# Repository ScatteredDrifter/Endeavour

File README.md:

# Endeavour | 10 Ortho Keyboard

An orthogonal  10u keyboard heavily inspired by [kb_elmo`s QEZ](https://github.com/kb-elmo/QEZ)

Used License for this project :: [Cern Open Hardware](/LICENSE)
by Evelyn~ Scattered Drifter 

---

### Current Status: 

- rev3 tested, minor issues fixed in 
- firmware for QMK was updated to newest version, can be found [here](https://github.com/ScatteredDrifter/vial-qmk/tree/scatteredDriftersBoards/keyboards/scattereddrifter/endeavour)
- ZMK firmware pending
- rev3 case available - yet I dislike it in its current state.

---

## Endeavour V³ released //
The third iteration introduced a complete redesign of the pcb primarily to accommodate the **RP2040** and **BAV70 diodes**.

 I tried creating a circular positioning pattern for the components where their center is set with the mcu itself. Due to reposition of every component I rerouted the whole board again; also because Endeavour V¹ was one of my first designs and you can tell it was. A new silkscreen for both front and back of the pcb sets a different theme and clutters the whole board with ASCII-rubbish. This came into my mind because any actual drawing or pattern idea I had was blocked by my miserable ability to create art.

A new **case** accompanies this revision. Its not entirely done neither am I satisfied with its look and design. My abilities with CAD are limited and I lack the endurance ( will to use Windows or learn an alternative software) and time to make a better one or to create an actual good / decent design. 

Nevertheless my current process is shared in [this folder](/cases_rev3).
I've **tested the case** with a previous rev pcb and could verify that its mostly working. 
The new **case utilizes tadpole mount** of some sort hence I **ought to write a build guide**. 

For the previous versions of the **PCB** and **Case** look at the folders below:

2. [Rev2](/rev2/rev2.md)

### Features |- Rev3:
- support for two encoders ( top left)(bottom row middle)
- RP2040 
- 3 IO Pins exposed via breakout 
- pinout for led-strip (WS28 and similarly supported)
- QMK / VIAL support ( zmk should be possible too ) 
- different layout options
- new **case** with tadpole mount

#### Layout:

---

## Images 

### Images of V³ PCB:

### Images of V³ case:
Those are only renders, however I've printed a small test version already. 

---

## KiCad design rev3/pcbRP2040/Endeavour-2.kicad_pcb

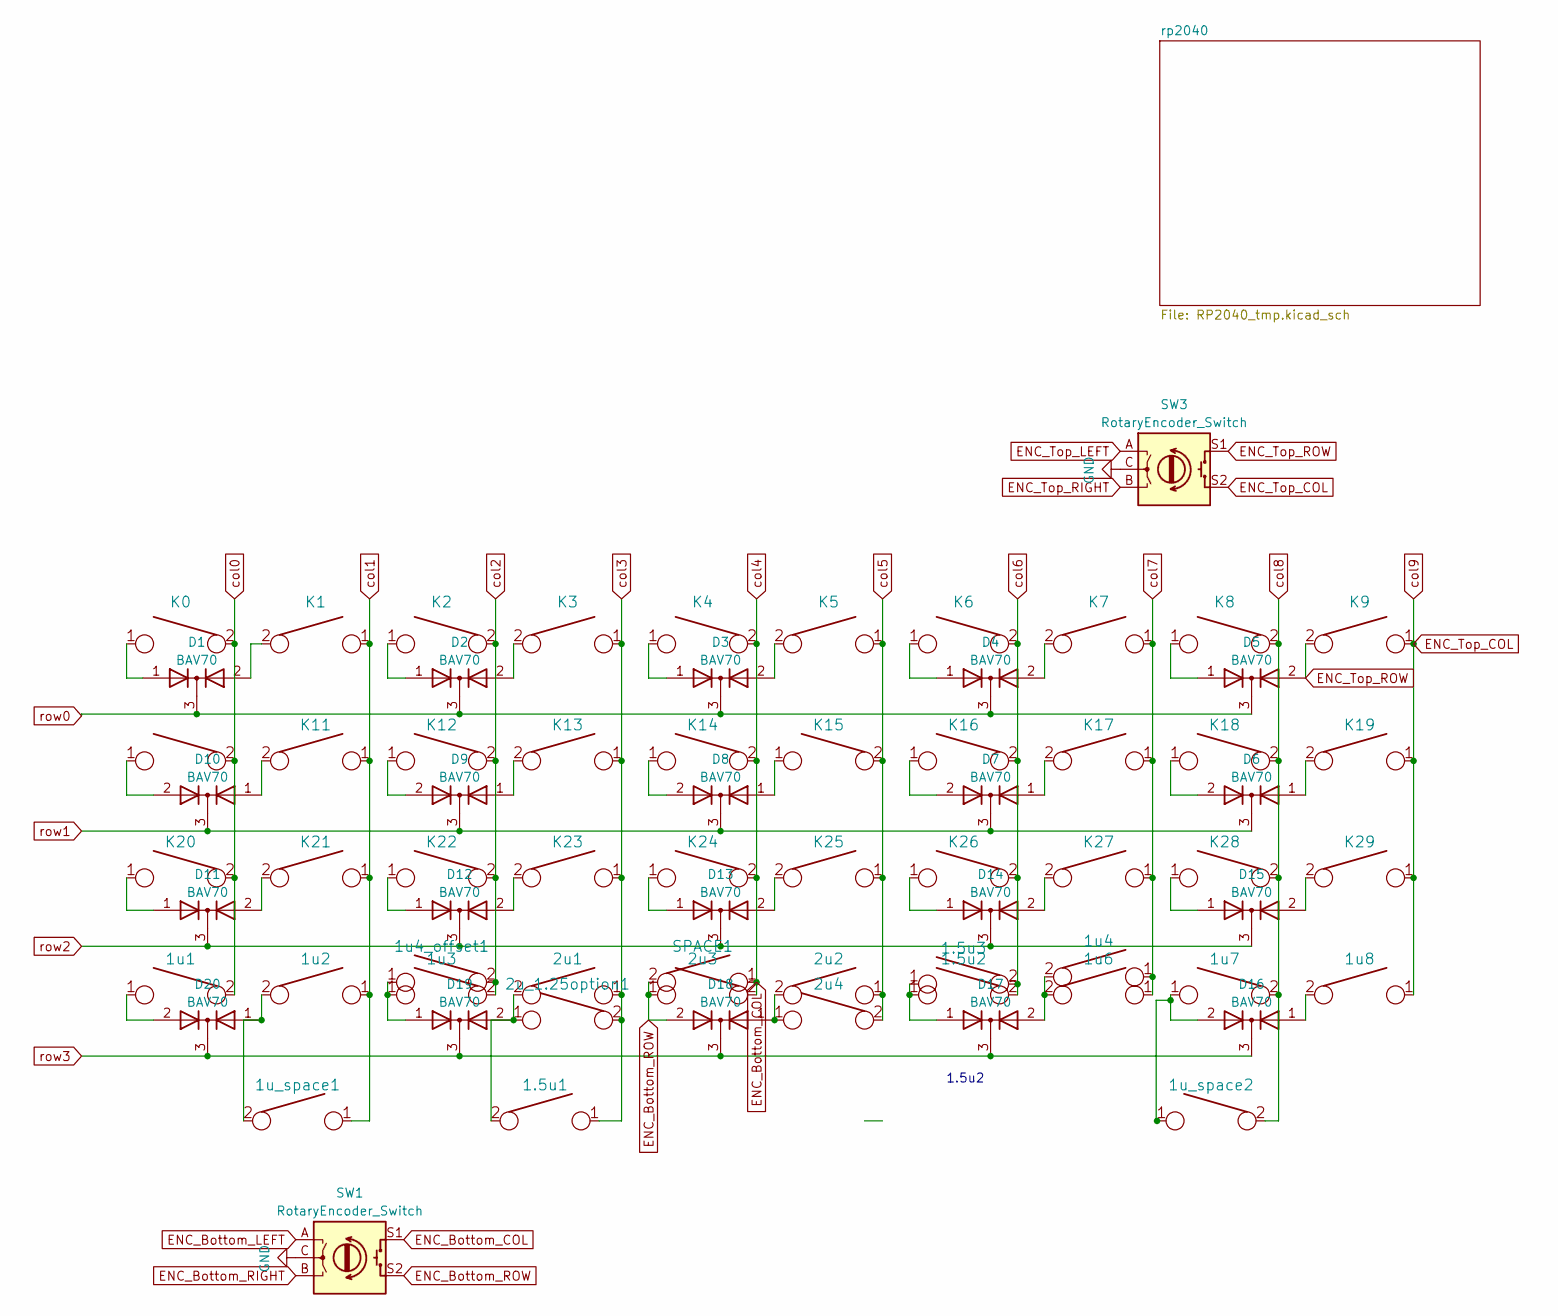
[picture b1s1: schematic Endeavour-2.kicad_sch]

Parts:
1.5u1, 1.5u2, 1.5u3: 1.5u; SW_MX_HS_1u_NOREF
1u1, 1u2, 1u3, 1u4, 1u4_offset1, 1u6, 1u7, 1u8, 1u_space1, 1u_space2: 1u; SW_MX_HS_1u_NOREF
2u1, 2u2, 2u3, 2u4, 2u_1.25option1: 2u; SW_MX_HS_1u_NOREF
D1, D2, D3, D4, D5, D6, D7, D8, D9, D10, D11, D12, D13, D14, D15, D16, D17, D18, D19, D20: BAV70; SOT-23
K0, K1, K2, K3, K4, K5, K6, K7, K8, K9, K10, K11, K12, K13, K14, K15, K16, K17, K18, K19, K20, K21, K22, K23, K24, K25, K26, K27, K28, K29: 1u; SW_MX_HS_1u_NOREF
SPACE1: 7u; SW_MX_HS_1u_NOREF
SW1, SW3: RotaryEncoder_Switch; ROT_Alps_EC11E-Switch

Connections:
ENC_Bottom_COL: 2u3.2, K4.2, K14.2, K24.2, SPACE1.1, SW1.S1; also elsewhere on the board
ENC_Bottom_LEFT: SW1.A; also elsewhere on the board
ENC_Bottom_RIGHT: SW1.B; also elsewhere on the board
ENC_Bottom_ROW: 2u3.1, D18.2 (A), SPACE1.2, SW1.S2
ENC_Top_COL: 1u8.1, K9.1, K19.1, K29.1, SW3.S2; also elsewhere on the board
ENC_Top_LEFT: SW3.A; also elsewhere on the board
ENC_Top_RIGHT: SW3.B; also elsewhere on the board
ENC_Top_ROW: D5.2 (A), K9.2, SW3.S1
GND: SW1.C, SW3.C; also elsewhere on the board
unnamed: 1.5u1.2, 2u1.2, 2u_1.25option1.1, D19.2 (A)
unnamed: 1.5u2.1, 1.5u3.1, D17.1 (A)
unnamed: 1u1.1, D20.2 (A)
unnamed: 1u2.2, 1u_space1.2, D20.1 (A)
unnamed: 1u3.1, 1u4_offset1.1, D19.1 (A)
unnamed: 1u4.2, 1u6.2, D17.2 (A)
unnamed: 1u7.1, 1u_space2.1, D16.2 (A)
unnamed: 1u8.2, D16.1 (A)
unnamed: 2u2.2, 2u4.1, D18.1 (A)
unnamed: D1.1 (A), K0.1
unnamed: D1.2 (A), K1.2
unnamed: D2.1 (A), K2.1
unnamed: D2.2 (A), K3.2
unnamed: D3.1 (A), K4.1
unnamed: D3.2 (A), K5.2
unnamed: D4.1 (A), K6.1
unnamed: D4.2 (A), K7.2
unnamed: D5.1 (A), K8.1
unnamed: D6.1 (A), K19.2
unnamed: D6.2 (A), K18.1
unnamed: D7.1 (A), K17.2
unnamed: D7.2 (A), K16.1
unnamed: D8.1 (A), K15.1
unnamed: D8.2 (A), K14.1
unnamed: D9.1 (A), K13.2
unnamed: D9.2 (A), K12.1
unnamed: D10.1 (A), K11.2
unnamed: D10.2 (A), K10.1
unnamed: D11.1 (A), K20.1
unnamed: D11.2 (A), K21.2
unnamed: D12.1 (A), K22.1
unnamed: D12.2 (A), K23.2
unnamed: D13.1 (A), K24.1
unnamed: D13.2 (A), K25.2
unnamed: D14.1 (A), K26.1
unnamed: D14.2 (A), K27.2
unnamed: D15.1 (A), K28.1
unnamed: D15.2 (A), K29.2
col0: 1u1.2, K0.2, K10.2, K20.2; also elsewhere on the board
col1: 1u2.1, 1u_space1.1, K1.1, K11.1, K21.1; also elsewhere on the board
col2: 1u3.2, 1u4_offset1.2, K2.2, K12.2, K22.2; also elsewhere on the board
col3: 1.5u1.1, 2u1.1, 2u_1.25option1.2, K3.1, K13.1, K23.1; also elsewhere on the board
col5: 2u2.1, 2u4.2, K5.1, K15.2, K25.1; also elsewhere on the board
col6: 1.5u2.2, 1.5u3.2, K6.2, K16.2, K26.2; also elsewhere on the board
col7: 1u4.1, 1u6.1, K7.1, K17.1, K27.1; also elsewhere on the board
col8: 1u7.2, 1u_space2.2, K8.2, K18.2, K28.2; also elsewhere on the board
row0: D1.3 (K), D2.3 (K), D3.3 (K), D4.3 (K), D5.3 (K); also elsewhere on the board
row1: D6.3 (K), D7.3 (K), D8.3 (K), D9.3 (K), D10.3 (K); also elsewhere on the board
row2: D11.3 (K), D12.3 (K), D13.3 (K), D14.3 (K), D15.3 (K); also elsewhere on the board
row3: D16.3 (K), D17.3 (K), D18.3 (K), D19.3 (K), D20.3 (K); also elsewhere on the board

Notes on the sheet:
1.5u2

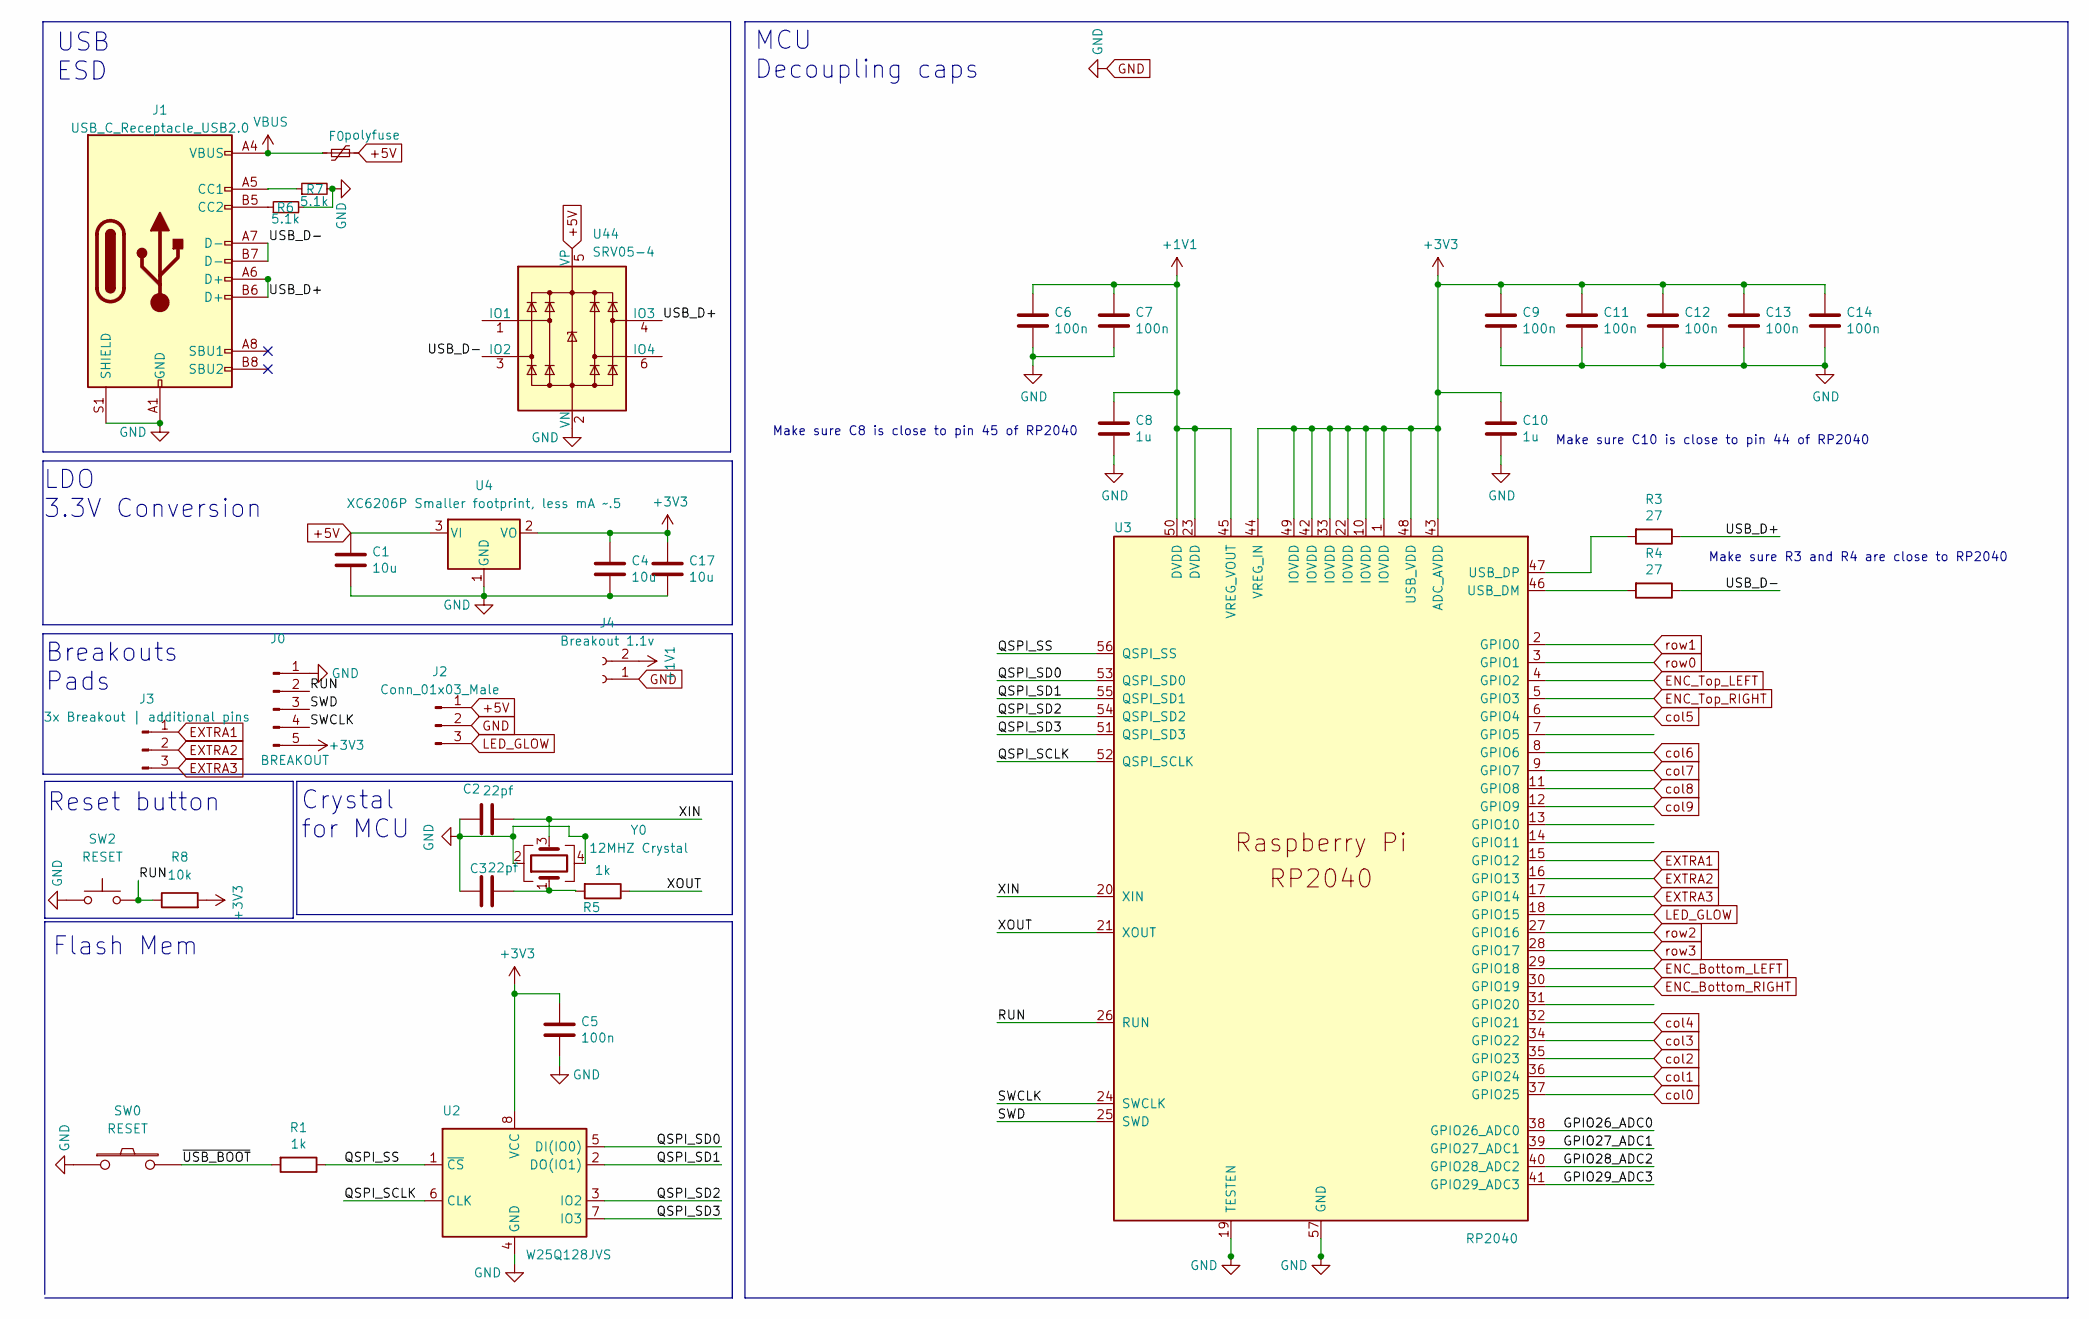
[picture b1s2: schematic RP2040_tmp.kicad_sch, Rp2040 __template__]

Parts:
C1, C4, C17: 10u; C_0805_2012Metric; LCSC C91245
C2, C3: 22pf; C_0805_2012Metric; LCSC C1804
C5, C6, C7, C9, C11, C12, C13, C14: 100n; C_0805_2012Metric; LCSC C49678
C8, C10: 1u; C_0805_2012Metric; LCSC C28323
F0: polyfuse; Fuse_1206_3216Metric; LCSC C69688
J0: BREAKOUT; PinSocket_1x05_P2.54mm_Vertical
J1: USB_C_Receptacle_USB2.0; USB_C_Receptacle_HRO_TYPE-C-31-M-12; LCSC C165948
J2: Conn_01x03_Male; PinSocket_1x03_P2.00mm_Vertical
J3: 3x Breakout | additional pins; PinHeader_1x03_P2.54mm_Vertical
J4: Breakout 1.1v; PinHeader_1x02_P2.54mm_Vertical
R1, R5: 1k; R_0805_2012Metric; LCSC C115316
R3, R4: 27; R_0805_2012Metric; LCSC C104170
R6, R7: 5.1k; R_0805_2012Metric; LCSC C27834
R8: 10k; R_0805_2012Metric; LCSC C115309
SW0, SW2: RESET; SW_SPST_TL3342; LCSC C2886894
U2: W25Q128JVS; SOIC-8_5.23x5.23mm_P1.27mm; LCSC C97521
U3: RP2040; RP2040-QFN-56; LCSC C2040
U4: XC6206P Smaller footprint, less mA ~.5; SOT-23; LCSC C347376
U44: SRV05-4; SOT-23-6; LCSC C85364
Y0: 12MHZ Crystal; Crystal_SMD_3225-4Pin_3.2x2.5mm; LCSC C9002

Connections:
+1V1: C6.1, C7.1, C8.1, J4.2, U3.23 (DVDD), U3.45 (VREG_VOUT), U3.50 (DVDD)
+3V3: C4.1, C5.1, C9.1, C10.1, C11.1, C12.1, C13.1, C14.1, C17.1, J0.5, R8.2, U2.8 (VCC), U3.1 (IOVDD), U3.10 (IOVDD), U3.22 (IOVDD), U3.33 (IOVDD), U3.42 (IOVDD), U3.43 (ADC_AVDD), U3.44 (VREG_IN), U3.48 (USB_VDD), U3.49 (IOVDD), U4.2 (VO)
+5V: C1.1, F0.2, J2.1, U4.3 (VI), U44.5 (VP)
/rp2040/GPIO26_ADC0: U3.38 (GPIO26_ADC0)
/rp2040/GPIO27_ADC1: U3.39 (GPIO27_ADC1)
/rp2040/GPIO28_ADC2: U3.40 (GPIO28_ADC2)
/rp2040/GPIO29_ADC3: U3.41 (GPIO29_ADC3)
/rp2040/QSPI_SCLK: U2.6 (CLK), U3.52 (QSPI_SCLK)
/rp2040/QSPI_SD0: U2.5 (DI(IO0)), U3.53 (QSPI_SD0)
/rp2040/QSPI_SD1: U2.2 (DO(IO1)), U3.55 (QSPI_SD1)
/rp2040/QSPI_SD2: U2.3 (IO2), U3.54 (QSPI_SD2)
/rp2040/QSPI_SD3: U2.7 (IO3), U3.51 (QSPI_SD3)
/rp2040/QSPI_SS: R1.1, U2.1 (~CS), U3.56 (QSPI_SS)
/rp2040/RUN: J0.2, R8.1, SW2.2, U3.26 (RUN)
/rp2040/SWCLK: J0.4, U3.24 (SWCLK)
/rp2040/SWD: J0.3, U3.25 (SWD)
/rp2040/USB_D+: J1.A6 (D+), J1.B6 (D+), R3.1, U44.4 (IO3)
/rp2040/USB_D-: J1.A7 (D-), J1.B7 (D-), R4.1, U44.3 (IO2)
/rp2040/XIN: C2.1, U3.20 (XIN), Y0.3
/rp2040/XOUT: R5.1, U3.21 (XOUT)
/rp2040/~USB_BOOT: R1.2, SW0.2
ENC_Bottom_COL: U3.32 (GPIO21); also elsewhere on the board
ENC_Bottom_LEFT: U3.29 (GPIO18); also elsewhere on the board
ENC_Bottom_RIGHT: U3.30 (GPIO19); also elsewhere on the board
ENC_Top_COL: U3.12 (GPIO9); also elsewhere on the board
ENC_Top_LEFT: U3.4 (GPIO2); also elsewhere on the board
ENC_Top_RIGHT: U3.5 (GPIO3); also elsewhere on the board
EXTRA1: J3.1, U3.15 (GPIO12)
EXTRA2: J3.2, U3.16 (GPIO13)
EXTRA3: J3.3, U3.17 (GPIO14)
GND: C1.2, C2.2, C3.2, C4.2, C5.2, C6.2, C7.2, C8.2, C9.2, C10.2, C11.2, C12.2, C13.2, C14.2, C17.2, J0.1, J1.A1 (GND), J1.A12 (GND), J1.B1 (GND), J1.B12 (GND), J1.S1 (SHIELD), J2.2, J4.1, R6.2, R7.2, SW0.1, SW2.1, U2.4 (GND), U3.19 (TESTEN), U3.57 (GND), U4.1 (GND), U44.2 (VN), Y0.2, Y0.4; also elsewhere on the board
LED_GLOW: J2.3, U3.18 (GPIO15)
unnamed: C3.1, R5.2, Y0.1
unnamed: J1.A5 (CC1), R7.1
unnamed: J1.B5 (CC2), R6.1
unnamed: R4.2, U3.46 (USB_DM)
unnamed: R3.2, U3.47 (USB_DP)
VBUS: F0.1, J1.A4 (VBUS), J1.A9 (VBUS), J1.B4 (VBUS), J1.B9 (VBUS)
col0: U3.37 (GPIO25); also elsewhere on the board
col1: U3.36 (GPIO24); also elsewhere on the board
col2: U3.35 (GPIO23); also elsewhere on the board
col3: U3.34 (GPIO22); also elsewhere on the board
col5: U3.6 (GPIO4); also elsewhere on the board
col6: U3.8 (GPIO6); also elsewhere on the board
col7: U3.9 (GPIO7); also elsewhere on the board
col8: U3.11 (GPIO8); also elsewhere on the board
row0: U3.3 (GPIO1); also elsewhere on the board
row1: U3.2 (GPIO0); also elsewhere on the board
row2: U3.27 (GPIO16); also elsewhere on the board
row3: U3.28 (GPIO17); also elsewhere on the board

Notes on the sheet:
USB ESD
Make sure C8 is close to pin 45 of RP2040
Breakouts Pads
Make sure R3 and R4 are close to RP2040
Crystal for MCU
Flash Mem
MCU Decoupling caps
Make sure C10 is close to pin 44 of RP2040
Reset button
LDO 3.3V Conversion

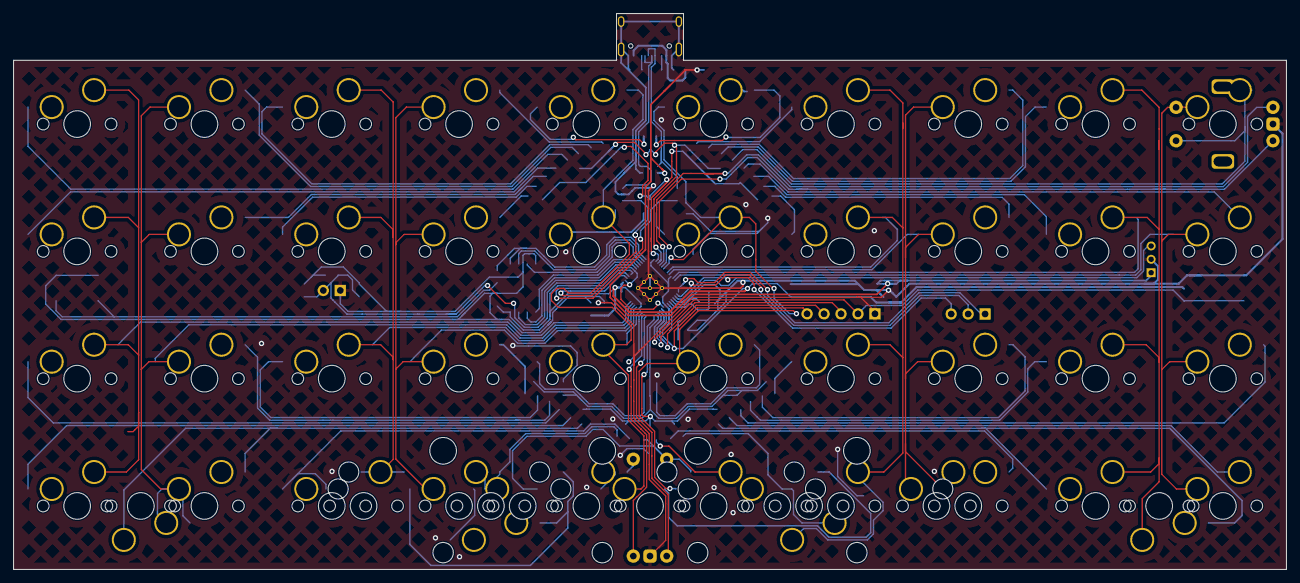
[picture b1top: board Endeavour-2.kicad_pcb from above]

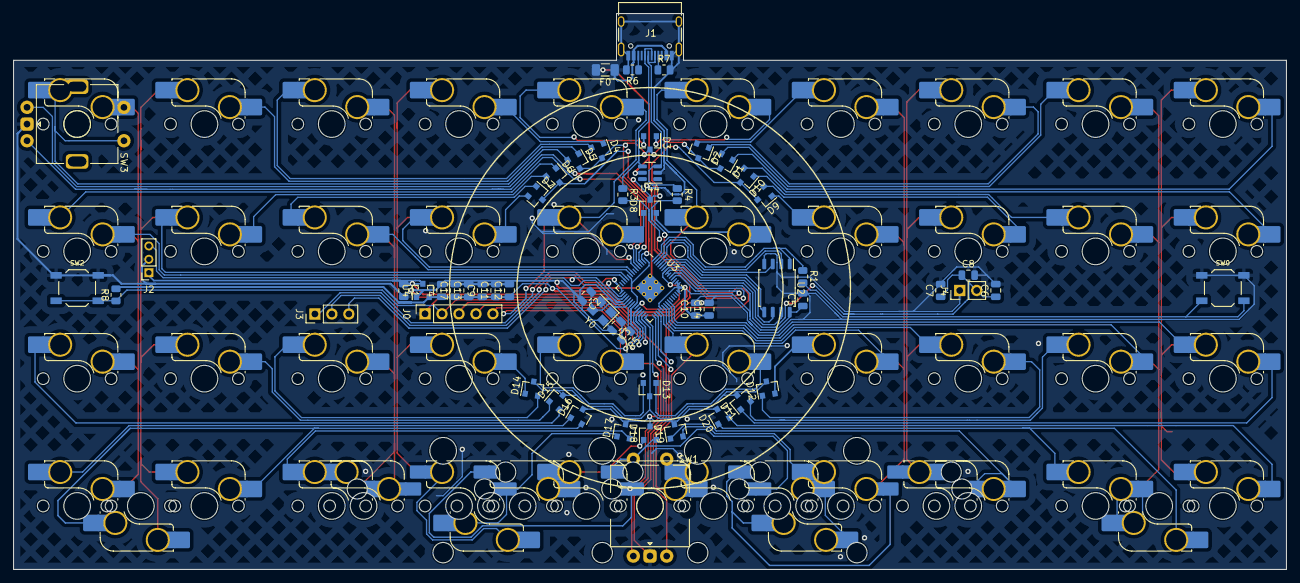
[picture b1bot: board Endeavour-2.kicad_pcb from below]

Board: 2 copper layers, 190.5 x 83.2 mm, 106 parts (106 on the bottom side), 86 nets.

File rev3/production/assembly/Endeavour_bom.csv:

Comment,Designator,Footprint,LCSC
"1.5u","1.5u1,1.5u2,1.5u3","marbastlib-mx:SW_MX_HS_1u_NOREF",""
"1u","K0,K1,K2,K3,K4,K5,K6,K7,K8,K9,K10,1u1,1u_space1,K11,1u2,1u_space2,K12,1u3,K13,1u4,K14,K15,1u6,K16,1u7,K17,1u8,K18,K19,K20,K21,K22,K23,K24,K25,K26,K27,K28,K29,1u4_offset1","marbastlib-mx:SW_MX_HS_1u_NOREF",""
"2u","2u1,2u2,2u3,2u4,2u_1.25option1","marbastlib-mx:SW_MX_HS_1u_NOREF",""
"10u","C1,C4,C17","Capacitor_SMD:C_0805_2012Metric","C91245"
"22pf","C2,C3","Capacitor_SMD:C_0805_2012Metric","C1804"
"100n","C5,C6,C7,C9,C11,C12,C13,C14","Capacitor_SMD:C_0805_2012Metric","C49678"
"1u","C8,C10","Capacitor_SMD:C_0805_2012Metric","C28323"
"BAV70","D1,D2,D3,D4,D5,D6,D7,D8,D9,D10,D11,D12,D13,D14,D15,D16,D17,D18,D19,D20","Package_TO_SOT_SMD:SOT-23","C181110"
"polyfuse","F0","Fuse:Fuse_1206_3216Metric","C69688"
"BREAKOUT","J0","Connector_PinSocket_2.54mm:PinSocket_1x05_P2.54mm_Vertical",""
"USB_C_Receptacle_USB2.0","J1","Connector_USB:USB_C_Receptacle_HRO_TYPE-C-31-M-12","C165948"
"Conn_01x03_Male","J2","Connector_PinSocket_2.00mm:PinSocket_1x03_P2.00mm_Vertical",""
"3x Breakout | additional pins","J3","Connector_PinHeader_2.54mm:PinHeader_1x03_P2.54mm_Vertical",""
"Breakout 1.1v","J4","Connector_PinHeader_2.54mm:PinHeader_1x02_P2.54mm_Vertical",""
"1k","R1,R5","Resistor_SMD:R_0805_2012Metric","C115316"
"27","R3,R4","Resistor_SMD:R_0805_2012Metric","C104170"
"5.1k","R6,R7","Resistor_SMD:R_0805_2012Metric","C27834"
"10k","R8","Resistor_SMD:R_0805_2012Metric","C115309"
"7u","SPACE1","marbastlib-mx:SW_MX_HS_1u_NOREF",""
"RESET ","SW0","Keebio-Parts:SW_SPST_TL3342","C2886894"
"RotaryEncoder_Switch","SW1,SW3","marbastlib-various:ROT_Alps_EC11E-Switch",""
"RESET","SW2","Keebio-Parts:SW_SPST_TL3342","C2886894"
"W25Q128JVS","U2","Package_SO:SOIC-8_5.23x5.23mm_P1.27mm","C97521"
"RP2040","U3","RP2040:RP2040-QFN-56","C2040"
"XC6206P Smaller footprint, less mA ~.5","U4","Package_TO_SOT_SMD:SOT-23","C347376"
"SRV05-4","U44","Package_TO_SOT_SMD:SOT-23-6","C85364"
"12MHZ Crystal ","Y0","Crystal:Crystal_SMD_3225-4Pin_3.2x2.5mm","C9002"

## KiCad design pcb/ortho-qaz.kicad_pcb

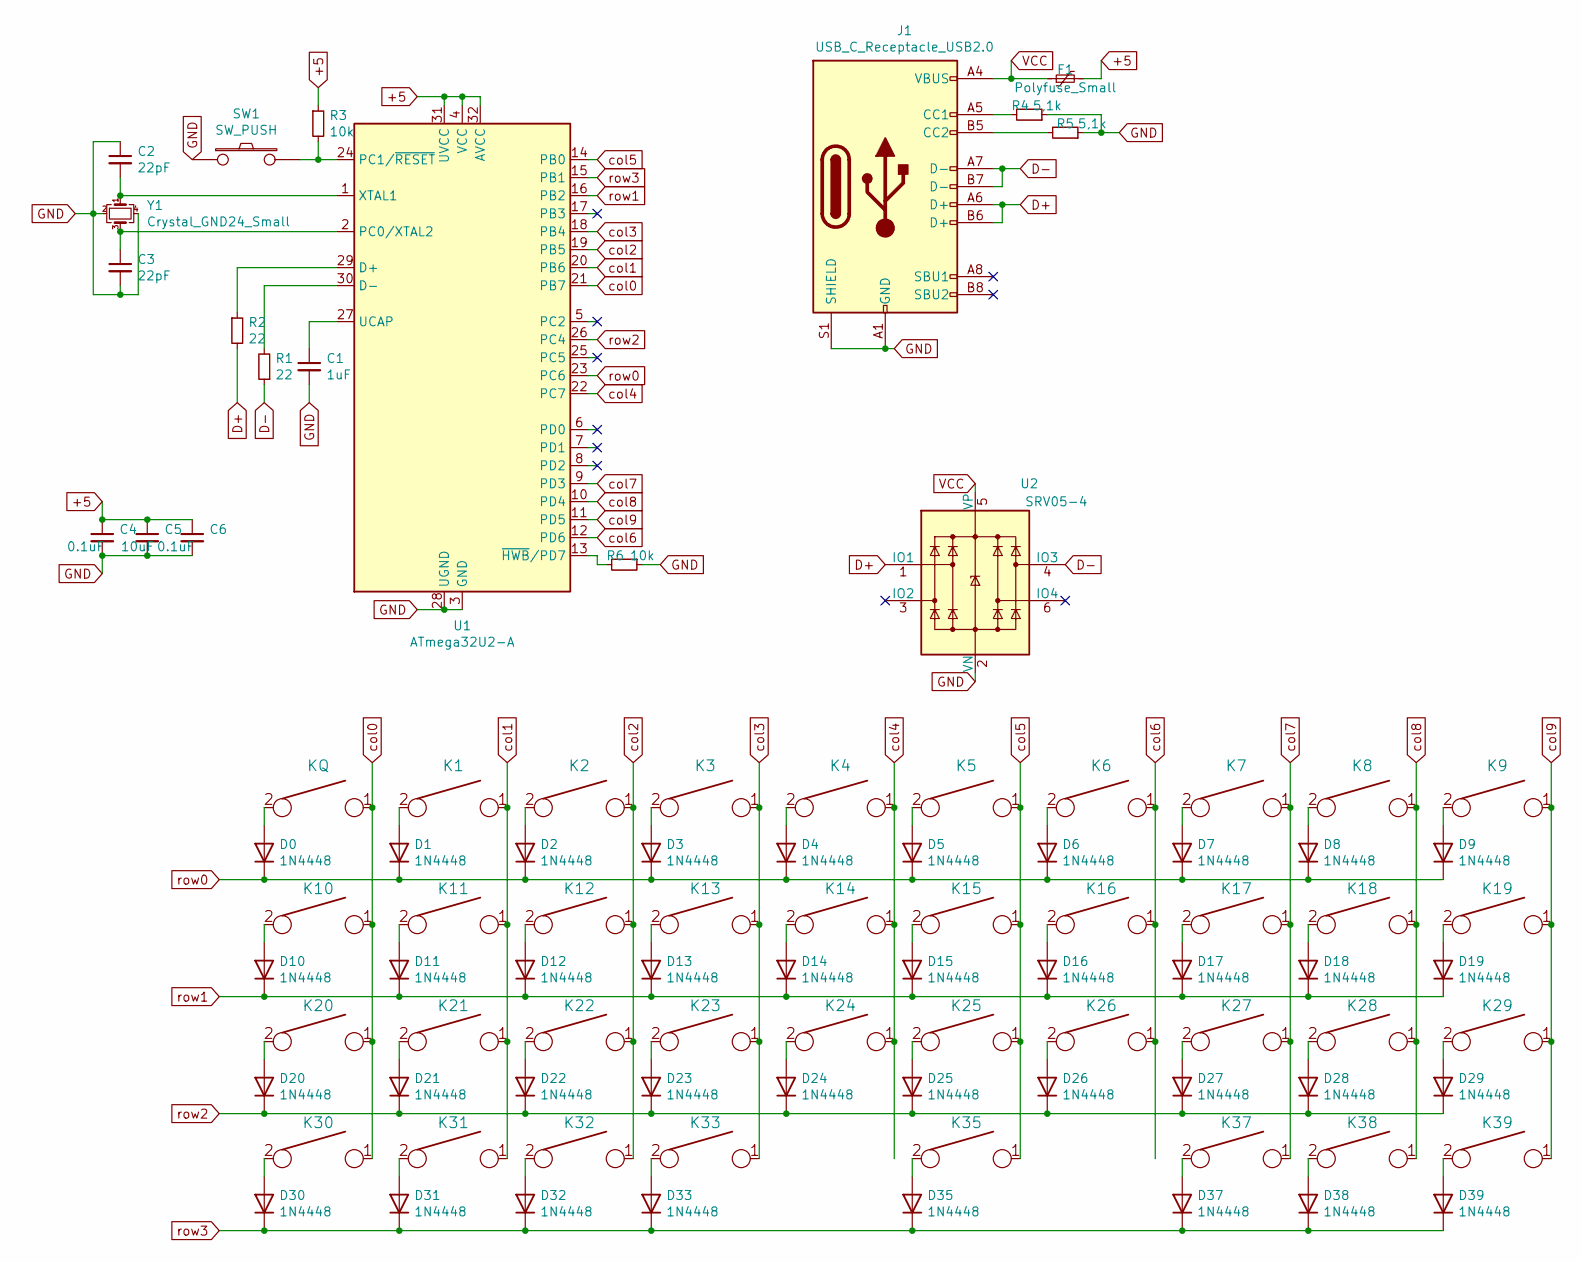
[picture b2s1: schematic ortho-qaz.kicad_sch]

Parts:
C1: 1uF; C_0805_2012Metric; LCSC C28323
C2, C3: 22pF; C_0805_2012Metric; LCSC C1804
C4, C6: 0.1uF; C_0805_2012Metric; LCSC C49678
C5: 10uF; C_0805_2012Metric; LCSC C91245
D0, D1, D2, D3, D4, D5, D6, D7, D8, D9, D10, D11, D12, D13, D14, D15, D16, D17, D18, D19, D20, D21, D22, D23, D24, D25, D26, D27, D28, D29, D30, D31, D32, D33, D35, D37, D38, D39: 1N4448; D_SOD123; LCSC C2128
F1: Polyfuse_Small; Fuse_1206_3216Metric; LCSC C69688
J1: USB_C_Receptacle_USB2.0; USB_C_Receptacle_HRO_TYPE-C-31-M-12; LCSC C165948
K1, K2, K3, K4, K5, K6, K7, K8, K9, K10, K11, K12, K13, K14, K15, K16, K17, K18, K19, K20, K21, K22, K23, K24, K25, K26, K27, K28, K29, K30, K31, K32, K33, K35, K37, K38, K39: KEYSW; Kailh_socket_MX_optional
KQ: KEYSW; Kailh_socket_MX_optional
R1, R2: 22; R_0805_2012Metric; LCSC C17561
R3, R6: 10k; R_0805_2012Metric; LCSC C17414
R4, R5: 5,1k; R_0805_2012Metric; LCSC C27834
SW1: SW_PUSH; SW_SPST_TL3342; LCSC C318884
U1: ATmega32U2-A; TQFP-32_7x7mm_P0.8mm; LCSC C618733
U2: SRV05-4; SOT-23-6; LCSC C85364
Y1: Crystal_GND24_Small; Crystal_SMD_3225-4Pin_3.2x2.5mm; LCSC C13738

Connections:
+5: C4.1, C5.1, C6.1, F1.2, R3.1, U1.4 (VCC), U1.31 (UVCC), U1.32 (AVCC)
D+: J1.A6 (D+), J1.B6 (D+), R2.2, U2.1 (IO1)
D-: J1.A7 (D-), J1.B7 (D-), R1.1, U2.4 (IO3)
GND: C1.2, C2.1, C3.2, C4.2, C5.2, C6.2, J1.A1 (GND), J1.A12 (GND), J1.B1 (GND), J1.B12 (GND), J1.S1 (SHIELD), R4.1, R5.1, R6.1, SW1.1, U1.3 (GND), U1.28 (UGND), U2.2 (VN), Y1.2, Y1.4
unnamed: C1.1, U1.27 (UCAP)
unnamed: C2.2, U1.1 (XTAL1), Y1.1
unnamed: C3.1, U1.2 (PC0/XTAL2), Y1.3
unnamed 7: D0.2 (A), KQ.2; also elsewhere on the board
unnamed: D1.2 (A), K1.2
unnamed: D2.2 (A), K2.2
unnamed: D3.2 (A), K3.2
unnamed: D4.2 (A), K4.2
unnamed: D5.2 (A), K5.2
unnamed: D6.2 (A), K6.2
unnamed: D7.2 (A), K7.2
unnamed: D8.2 (A), K8.2
unnamed: D9.2 (A), K9.2
unnamed: D10.2 (A), K10.2
unnamed: D11.2 (A), K11.2
unnamed: D12.2 (A), K12.2
unnamed: D13.2 (A), K13.2
unnamed: D14.2 (A), K14.2
unnamed: D15.2 (A), K15.2
unnamed: D16.2 (A), K16.2
unnamed: D17.2 (A), K17.2
unnamed: D18.2 (A), K18.2
unnamed: D19.2 (A), K19.2
unnamed: D20.2 (A), K20.2
unnamed: D21.2 (A), K21.2
unnamed: D22.2 (A), K22.2
unnamed: D23.2 (A), K23.2
unnamed: D24.2 (A), K24.2
unnamed: D25.2 (A), K25.2
unnamed: D26.2 (A), K26.2
unnamed: D27.2 (A), K27.2
unnamed: D28.2 (A), K28.2
unnamed: D29.2 (A), K29.2
unnamed: D30.2 (A), K30.2
unnamed: D31.2 (A), K31.2
unnamed: D32.2 (A), K32.2
unnamed: D33.2 (A), K33.2
unnamed: D35.2 (A), K35.2
unnamed: D37.2 (A), K37.2
unnamed: D38.2 (A), K38.2
unnamed: D39.2 (A), K39.2
unnamed: J1.A5 (CC1), R4.2
unnamed: J1.B5 (CC2), R5.2
unnamed: R1.2, U1.30 (D-)
unnamed: R2.1, U1.29 (D+)
unnamed: R3.2, SW1.2, U1.24 (PC1/~RESET)
unnamed: R6.2, U1.13 (~HWB/PD7)
VCC: F1.1, J1.A4 (VBUS), J1.A9 (VBUS), J1.B4 (VBUS), J1.B9 (VBUS), U2.5 (VP)
col0: K10.1, K20.1, K30.1, KQ.1, U1.21 (PB7); also elsewhere on the board
col1: K1.1, K11.1, K21.1, K31.1, U1.20 (PB6)
col2: K2.1, K12.1, K22.1, K32.1, U1.19 (PB5)
col3: K3.1, K13.1, K23.1, K33.1, U1.18 (PB4)
col4: K4.1, K14.1, K24.1, U1.22 (PC7)
col5: K5.1, K15.1, K25.1, K35.1, U1.14 (PB0)
col6: K6.1, K16.1, K26.1, U1.12 (PD6)
col7: K7.1, K17.1, K27.1, K37.1, U1.9 (PD3)
col8: K8.1, K18.1, K28.1, K38.1, U1.10 (PD4)
col9: K9.1, K19.1, K29.1, K39.1, U1.11 (PD5)
row0: D0.1 (K), D1.1 (K), D2.1 (K), D3.1 (K), D4.1 (K), D5.1 (K), D6.1 (K), D7.1 (K), D8.1 (K), D9.1 (K), U1.23 (PC6)
row1: D10.1 (K), D11.1 (K), D12.1 (K), D13.1 (K), D14.1 (K), D15.1 (K), D16.1 (K), D17.1 (K), D18.1 (K), D19.1 (K), U1.16 (PB2)
row2: D20.1 (K), D21.1 (K), D22.1 (K), D23.1 (K), D24.1 (K), D25.1 (K), D26.1 (K), D27.1 (K), D28.1 (K), D29.1 (K), U1.26 (PC4)
row3: D30.1 (K), D31.1 (K), D32.1 (K), D33.1 (K), D35.1 (K), D37.1 (K), D38.1 (K), D39.1 (K), U1.15 (PB1)

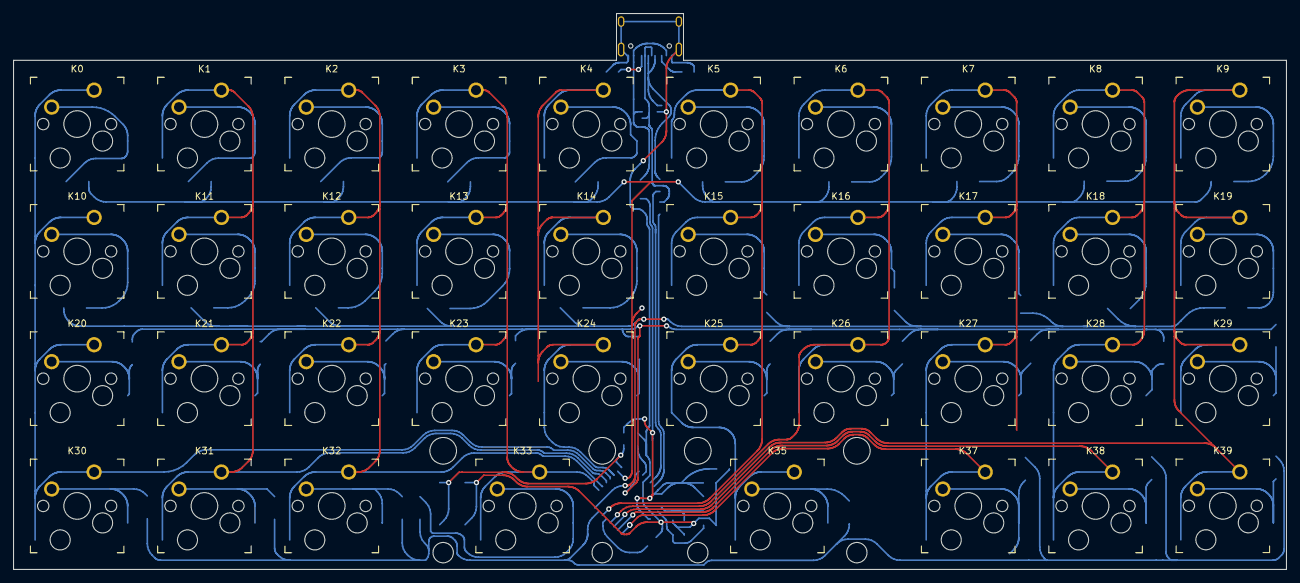
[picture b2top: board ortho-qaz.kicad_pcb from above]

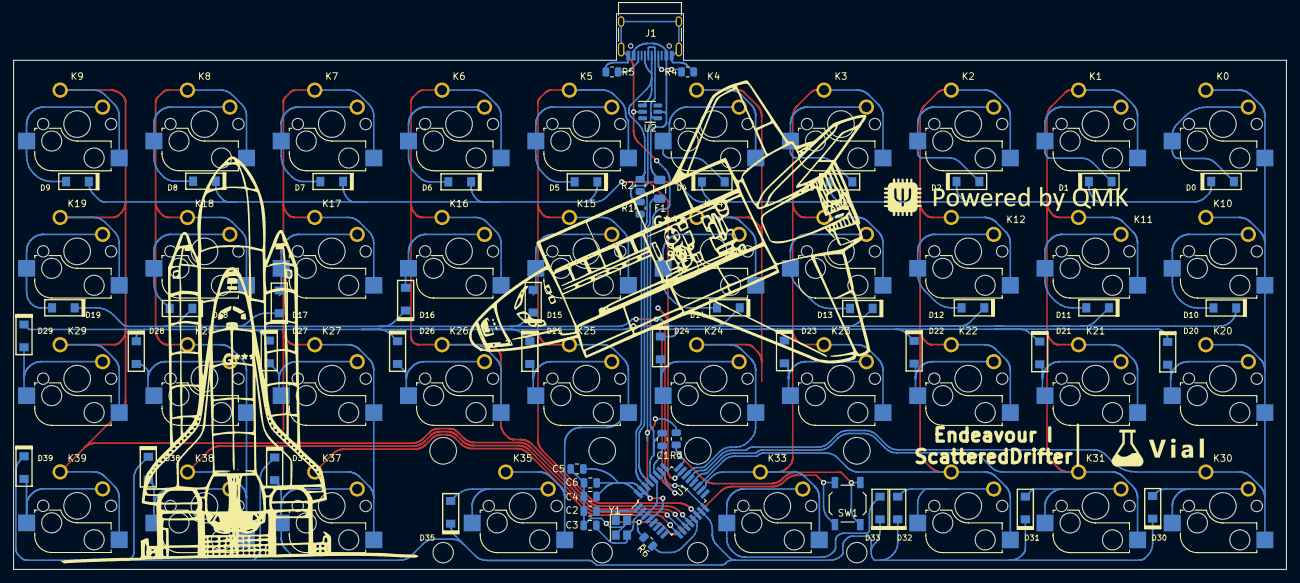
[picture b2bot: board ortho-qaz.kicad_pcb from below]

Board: 2 copper layers, 190.5 x 83.2 mm, 94 parts (56 on the bottom side), 66 nets.

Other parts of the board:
K0: KEYSW; Kailh_socket_MX_optional

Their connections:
unnamed 7: K0.2; also elsewhere on the board
col0: K0.1; also elsewhere on the board

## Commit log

2021-11-28 added pcb, case and firmware files
2021-12-01 updated case, fixed screw hole and included .step
2021-12-03 updated case, fixed minor issues regarding dimensions of bottomcase
2021-12-11 updated README,new images,updated case, added wkl,hhkb,megahhkb options
2021-12-11 added cca
2021-12-12 added new bottom row options
2021-12-13 updated version of case - 5mm spacing between case and pcb, better screw placement,
2021-12-14 updated case to REV5.1
2022-01-12 added plates for layouts
2022-01-15 updated pcb to rev2, added new bom,gerber,pos; firmware for rev2
2022-01-15 split up README, updated READMES for rev1/2
2022-01-16 updated vial firmware to support all 9 bottom rows
2022-01-16 fixed README.md
2022-01-16 added 10 u support for vial
2022-03-09 fixed kle and firmware
2022-04-03 declustered, updated firmware folders
2023-04-02 added pcb based on rp2040
    - updated footprints to hotswap only
    - silkscreen not done yet
    - new positioning of diode cluster, updated to BAV70 diodes
    - further bottom-row options included
2023-04-02 clean,up of repo
2023-10-05 added new 3dp-case, updated pcb to rp204 and more
2023-10-06 updated links between revisions, restructured readme
2023-11-19 update readme, add images of pcb and update information
2024-03-17 fix overlapping footprint, add legends for bottom row
2024-03-17 reorganize repo, remove unused assets
2024-03-17 update readme, fix typos
